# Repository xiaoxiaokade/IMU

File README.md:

​      IMU_base_V7是IMU底板的第七版，更换了DCDC芯片，换成SY8303，电源已稳定，但电感选型有误，其饱和电流太小。

​     IMU_base_V7.1在IMU_base_V7的基础上，换了饱和电流更大的功率电感，并且改正了一些如丝印错误、元件位置放置不佳等小问题。

​     IMU_base_V7.2重新换回TD1469，并去掉了前馈电容，但是有一个奇怪的现象，在学生电源上电没问题，但使用电池上电就会烧。

​     IMU_BMI088是FPC软板。由于BMI088的工作温度在45°左右，故需将其与底板隔开。

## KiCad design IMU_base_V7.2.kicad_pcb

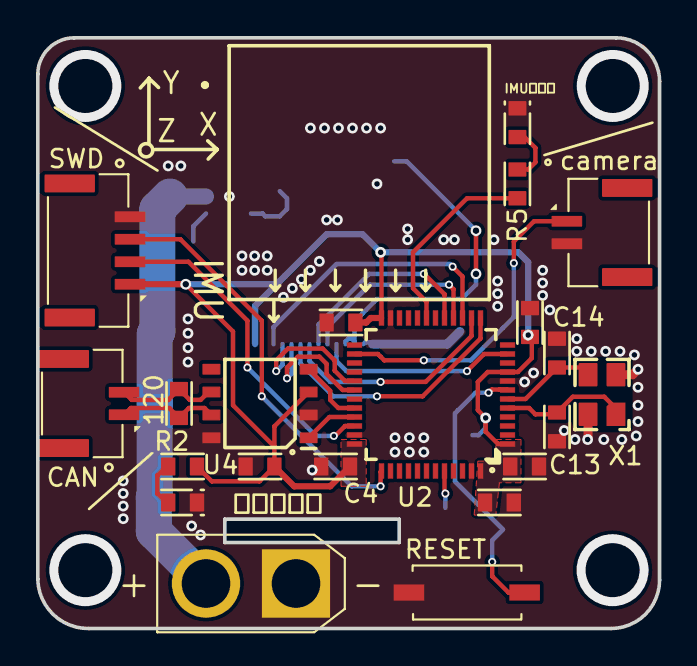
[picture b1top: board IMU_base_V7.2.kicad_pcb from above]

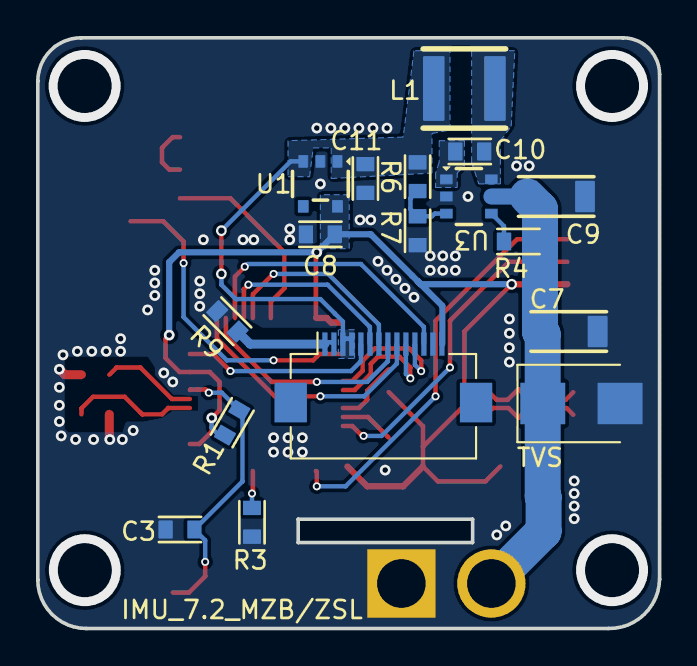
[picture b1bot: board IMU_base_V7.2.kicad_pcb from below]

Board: 2 copper layers, 34.5 x 32.8 mm, 38 parts (17 on the bottom side), 31 nets.

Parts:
120: 120R; R0603(1608M)
C1, C2, C3, C4, C5, C6: 104; C0603(1608M)
C7: 22uF/1206/35V; C1206(3216M)
C8, C11: 10uF; C0603(1608M)
C9: 22uF/35V/1206; C1206(3216M)
C10: 100nF; C0603(1608M)
C12: 10nF; C0603(1608M)
C13, C14: 18pF; C0603(1608M)
CAN: Conn_01x02; GH1.25_V_2
IMU指示灯: 蓝灯; LED0603(1608M)
J2: Conn_01x02; AMASS_XT30U-M_1x02_P5.0mm_Vertical
J4: Conn_01x14; Hirose_FH12-14S-0.5SH_1x14-1MP_P0.50mm_Horizontal
L1: 22uH; L_SWPA4030S
R1, R2, R3, R5: 1K; R0603(1608M)
R4: 100K; C0603(1608M)
R6: 43K; C0603(1608M)
R7: 8.2K; C0603(1608M)
R9: 0R; R0603(1608M)
RESET: SW_DIP_x01; Swith_3_6_2.5MM
SWD: Conn_01x04; GH1.25_V_4
TVS: Diode_TVS_Bi; D_SMB
U1: HX9193-33GB; SOT-23-5
U2: STM32F103C8Tx; QFP-7070_48
U3: TD1469; SOT-23-6
U4: VP230; SOP-3949_8
X1: Xtal-4; SMD-3225_4
camera: Conn_01x02; GH1.25_V_2
电源指示灯: 红灯; LED0603(1608M)

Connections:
+3V3: C1.1, C2.1, C4.1, C5.1, C6.1, C8.2, C12.2, J4.14, R1.1, R2.2, SWD.1, U1.5 (VOUT), U2.1 (Vbat), U2.9 (Vin_A), U2.24 (Vin), U2.36 (Vin), U2.48 (Vin), U4.3 (Vin)
+5V: C11.1, J4.3, J4.4, L1.2, R6.1, U1.1 (VIN), U1.3 (EN)
+24V: C7.1, C9.1, J2.2, R4.1, TVS.1 (Cathode), U3.5 (VIN)
/BOOT0: R3.1, U2.44 (BOOT0)
/CAN0_RX: U2.32 (PA11), U4.4 (Rx_D)
/CAN0_TX: U2.33 (PA12), U4.1 (Tx_D)
/CAN_H: 120.2, CAN.1, U4.7 (CAN_H)
/CAN_L: 120.1, CAN.2, U4.6 (CAN_L)
/CS1_Acce1: J4.11, U2.29 (PA8)
/CS1_Gyro: J4.10, U2.30 (PA9)
/INT1_Acce1: J4.9, U2.13 (PA3)
/INT1_Gyro: J4.8, U2.14 (PA4)
/LED: R5.2, U2.19 (PB1)
/RESET: C3.1, R1.2, RESET.1, U2.7 (nRST)
/SPI1_CLK: J4.12, U2.15 (PA5)
/SPI1_MISO: J4.6, U2.16 (PA6)
/SPI1_MOSI: J4.7, U2.17 (PA7)
/SWCLK: SWD.3, U2.37 (PA14)
/SWDIO: SWD.2, U2.34 (PA13)
/TIM10_CH1: J4.5, U2.11 (PA1)
/XTAL0: C13.2, U2.5 (PD0), X1.1
/XTAL1: C14.2, U2.6 (PD1), X1.3
GND: C1.2, C2.2, C3.2, C4.2, C5.2, C6.2, C7.2, C8.1, C9.2, C11.2, C12.1, C13.1, C14.1, IMU指示灯.1 (Cathode), J2.1, J4.13, R3.2, R7.1, R9.1, RESET.2, SWD.4, TVS.2 (Anode), U1.2 (GND), U2.8 (GND_A), U2.23 (GND), U2.35 (GND), U2.47 (GND), U3.2 (GND), U4.2 (GND), U4.8 (STB), X1.2, X1.4, camera.2, 电源指示灯.1 (Cathode)
GNDPWR: J4.1, J4.2, R9.2
unnamed: C10.1, U3.1 (BST)
unnamed: C10.2, L1.1, U3.6 (SW)
unnamed: R2.1, 电源指示灯.2 (Anode)
unnamed: IMU指示灯.2 (Anode), R5.1
unnamed: U2.26 (PB13), camera.1
unnamed: R4.2, U3.4 (EN)
unnamed: R6.2, R7.2, U3.3 (FB)

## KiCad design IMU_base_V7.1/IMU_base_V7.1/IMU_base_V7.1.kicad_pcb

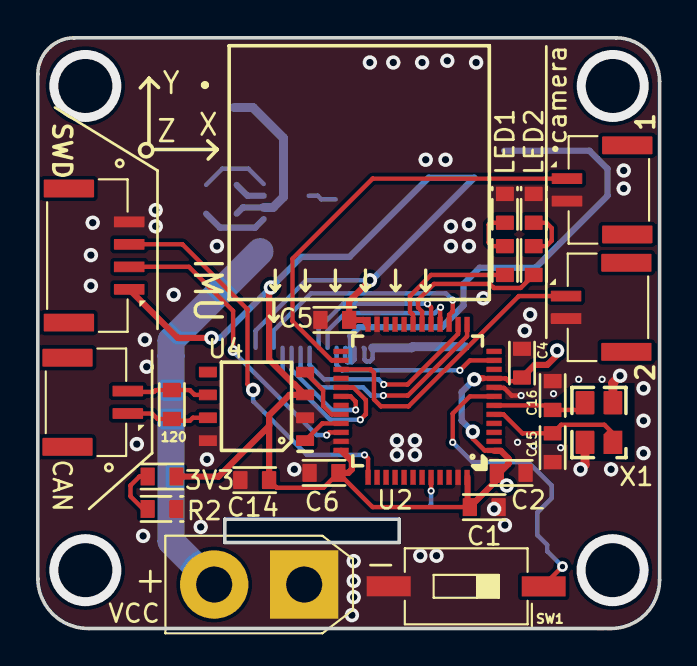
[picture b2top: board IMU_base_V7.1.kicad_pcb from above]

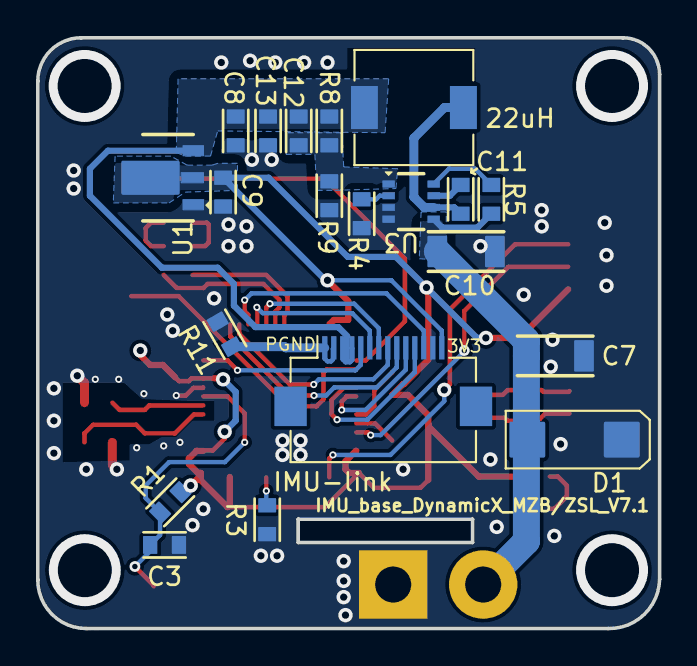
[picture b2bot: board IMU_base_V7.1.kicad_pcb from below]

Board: 2 copper layers, 34.5 x 32.8 mm, 44 parts (20 on the bottom side), 34 nets.

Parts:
3V3: 红灯; LED0603(1608M)
22uH: 22uH; L_6.3x6.3_H3
120: 120R; R0603(1608M)
C1, C2, C3, C4, C5, C6: 104; C0603(1608M)
C7: 22uF/1206/35V; C1206(3216M)
C8, C9: 10uF; C0603(1608M)
C10: 4.7uF/1206/35V; C1206(3216M)
C11, C12, C14: 10nF; C0603(1608M)
C13: 22uF; C0603(1608M)
C15, C16: 18pF; C0603(1608M)
D1: Diode_TVS_Bi; Suppresses_transient_diodes_IMU
J1: Conn_01x04; GH1.25_V_4
J3, J4, J6: Conn_01x02; GH1.25_V_2
J5: Conn_01x14; Hirose_FH12-14S-0.5SH_1x14-1MP_P0.50mm_Horizontal
LED1: 绿灯; LED0603(1608M)
LED2: 蓝灯; LED0603(1608M)
R1, R2, R3, R6, R7: 1K; R0603(1608M)
R4, R5: 100k; R0603(1608M)
R8: 150k; R0603(1608M)
R9: 20.5k; R0603(1608M)
R11: 0R; R0603(1608M)
SW1: SW_DIP_x01; SW_DIP_SPSTx01_Slide_6.7x4.1mm_W8.61mm_P2.54mm_LowProfile
U1: AMS1117; SOT-89
U2: STM32F103C8Tx; QFP-7070_48
U3: SY8303; SOT-23-8
U4: VP230; SOP-3949_8
VCC: Conn_01x02; AMASS_XT30U-M_1x02_P5.0mm_Vertical
X1: Xtal-4; SMD-3225_4

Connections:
+3V3: C1.1, C2.1, C4.1, C5.1, C6.1, C9.2, C14.2, J1.1, J5.14, R1.1, R2.2, U1.2 (VOUT), U2.1 (Vbat), U2.9 (Vin_A), U2.24 (Vin), U2.36 (Vin), U2.48 (Vin), U4.3 (Vin)
+5V: 22uH.2, C8.2, C12.2, C13.2, J5.3, J5.4, R8.1, U1.3 (VIN)
+24V: C7.1, C10.2, D1.1 (Cathode), R5.1, U3.5 (VIN), VCC.2
/BOOT0: R3.1, U2.44 (BOOT0)
/CAN0_RX: U2.32 (PA11), U4.4 (Rx_D)
/CAN0_TX: U2.33 (PA12), U4.1 (Tx_D)
/CAN_H: 120.2, J6.1, U4.7 (CAN_H)
/CAN_L: 120.1, J6.2, U4.6 (CAN_L)
/CS1_Acce1: J5.11, U2.29 (PA8)
/CS1_Gyro: J5.10, U2.30 (PA9)
/INT1_Acce1: J5.9, U2.13 (PA3)
/INT1_Gyro: J5.8, U2.14 (PA4)
/LED1: R7.2, U2.19 (PB1)
/RESET: C3.1, R1.2, SW1.1, U2.7 (nRST)
/SPI1_CLK: J5.12, U2.15 (PA5)
/SPI1_MISO: J5.6, U2.16 (PA6)
/SPI1_MOSI: J5.7, U2.17 (PA7)
/SWCLK: J1.3, U2.37 (PA14)
/SWDIO: J1.2, U2.34 (PA13)
/TIM10_CH1: J5.5, U2.11 (PA1)
/XTAL0: C15.2, U2.5 (PD0), X1.1
/XTAL1: C16.2, U2.6 (PD1), X1.3
GND: 3V3.1 (Cathode), C1.2, C2.2, C3.2, C4.2, C5.2, C6.2, C7.2, C8.1, C9.1, C10.1, C13.1, C14.1, C15.1, C16.1, D1.2 (Anode), J1.4, J3.2, J4.2, J5.13, LED1.1 (Cathode), LED2.1 (Cathode), R3.2, R4.1, R9.1, R11.1, SW1.2, U1.1 (GND), U2.8 (GND_A), U2.23 (GND), U2.35 (GND), U2.47 (GND), U3.3 (GND), U3.4 (GND), U4.2 (GND), U4.8 (STB), VCC.1, X1.2, X1.4
GNDPWR: J5.1, J5.2, R11.2
unnamed: C11.1, U3.7 (BST)
unnamed: 22uH.1, C11.2, U3.6 (SW)
unnamed: C12.1, R8.2, R9.2, U3.1 (FB)
unnamed: 3V3.2 (Anode), R2.1
unnamed: LED1.2 (Anode), R6.1
unnamed: LED2.2 (Anode), R7.1
unnamed: J3.1, U2.26 (PB13)
unnamed: J4.1, U2.27 (PB14)
unnamed: R4.2, U3.2 (FS)
unnamed: R5.2, U3.8 (EN)

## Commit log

2022-12-05 ADD IMU_base_V7 and V7.1
2022-12-05 README
    ​ IMU_base_V7是IMU底板的第七版，更换了DCDC芯片，换成SY8303，电源已稳定，但电感选型有误，其饱和电流太小。
    ​ IMU_base_V7.1在IMU_base_V7的基础上，换了饱和电流更大的功率电感，并且改正了一些如丝印错误、元件位置放置不佳等小问题。
    ​ IMU_BMI088是FPC软板。由于BMI088的工作温度在60°左右，故需将其与底板隔开。
2023-04-14 ADD IMU_BaseV7.2
2023-04-14 ADD IMU_base_V7.2
2023-04-14 change someting
